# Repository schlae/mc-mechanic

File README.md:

# MC Mechanic - POST card for Micro Channel Computers
If you have an IBM PS/2 computer or one of the rare non-IBM Micro Channel computers, you know how hard it can be to debug boot issues. The IBM BIOS designs often do not use the PC speaker as extensively as other BIOSes, and a POST card is pretty much a requirement. However, not many were made back in the day and they are quite rare.

Fortunately, there is now a solution, the MC Mechanic. Not only can you get the standard PS/2 checkpoint codes at address 680h, but you can also spy on other addresses, which can be useful for troubleshooting. An additional bonus feature is the PS/2 info panel display. This lets you to see additional messages on PS/2 systems whose BIOS supports it but do not have the display itself. The PS/2 model 77 is one example, but there are probably others.

The components are reasonably available. The bill of materials lists Mouser part numbers, but the devices are all pretty common and can be purchased from a variety of overseas sources.

Here are the design files.

[Schematic](https://github.com/schlae/mc-mechanic/blob/main/mcapostcard.pdf)

[Bill of Materials](https://github.com/schlae/mc-mechanic/blob/main/mcapostcard.csv)

The 0.1" header pins are *not* listed on the schematic. They are standard breakaaway headers. You don't even have to install them since they are for advanced debugging with HP logic analyzer pods.

If you do not need the info panel display, then do not populate U10 and U8.

The design uses three GAL devices; two for driving the hex displays and one for decoding the address of the info panel (U8). The BOM specifies ATF16V8 devices because these are easy to get. The speed grade doesn't matter.

[Fab Files](https://github.com/schlae/mc-mechanic/blob/main/fab/mcapostcard-rev2.zip)

## Fabrication Notes
This is a 2-layer board sized for the lowest cost. The board dimensions are 3.925" x 3.475" (100mm x 88mm).

When ordering the board, you **must** specify a card edge bevel of 20 degrees (details of the bevel are included in the Dwgs.User layer). This is **not** optional! The contacts in the Micro Channel socket are easily bent if you attempt to insert a card with no bevel. [Don't believe me? See this page.](https://www.ardent-tool.com/RS6000/RS6000_9-K.html#ECA265)

Ideally you should use selective gold plating (hard gold) for the edge fingers, but this can get expensive for small orders. ENIG will work but the gold will rub off fairly quickly.

For the soldermask color, pick whatever you want!

## Assembly Notes

After you solder in the components, be sure to solder two jumper wires in the J4 position with the two wires aligned vertically (see the photo above). This configures the board for using the "normal" version of the hex rotary switches. If you decided to use the "complemented" version, then solder two jumper wires aligned horizontally.

You probably want to install the two (or three) GAL devices in sockets, just in case. The popular Minipro device programmer can be used to flash the ATF16V8 devices.

The command line for that (under Linux) looks like

`minipro -p "ATF16V8B" -w hexlatch.jed -P`

Here are the JEDEC files:

[hexlatch.jed](https://github.com/schlae/mc-mechanic/blob/main/pld/hexlatch.jed) - U6 and U7

[addrlatch.jed](https://github.com/schlae/mc-mechanic/blob/main/pld/addrlatch.jed) - U8

## Using the Card
Be sure to dial in an address using the four hex rotary switches. Unlike ISA bus machines, Micro Channel machines typically use address 0680h, so set SW4=0, SW3=6, SW2=8, and SW1=0. Plug the card in the computer, being careful to make sure it is pointed the right way around (there is an arrow underneath the two electrolytic capacitors pointing to the rear of the case of the computer.) Turn on the computer, and you should see three green LEDs (for the power rails) and a two-digit code that increments as the computer boots up.

For the meaning of the codes, see [this list of checkpoint codes](https://ardent-tool.com/trouble/cp_codes.html).

Messages also show up at the printer port address, 03BC. But feel free to explore and snoop any address you want using the hex rotary switches. As long as it is an IO port address that the computer *writes* to during standard IO transfers (not setup transfers), you will see data.

### Troubleshooting for Engineers
If you have an HP logic analyzer, like a 1670 or 16700 series, you can connect two cables to the card using standard HP 01650-63203 termination adapters. The pin assignments are as follows:

| HP | J2   |    J3   |
|----|------|---------|
| CLK | CMD# | ADL# |
| D0 | CHRESET | A0  |
| D1 | MIO  | A1  |
| D2 | S0# | A2 |
| D3 | CD\_SETUP# | A3 |
| D4 | LED\_SEL# | A4 |
| D5 | SEL1\_CMD# | A5 |
| D6 | n/c | A6 |
| D7 | A0 (latched) | A7 |
| D8 | D0 | A8 |
| D9 | D1 | A9 |
| D10 | D2 | A10 |
| D11 | D3 | A11 |
| D12 | D4 | A12 |
| D13 | D5 | A13 |
| D14 | D6 | A14 |
| D15 | D7 | A15 |

## License

This work is licensed under a Creative Commons Attribution-ShareAlike 4.0
International License. See [https://creativecommons.org/licenses/by-sa/4.0/](https://creativecommons.org/licenses/by-sa/4.0/).

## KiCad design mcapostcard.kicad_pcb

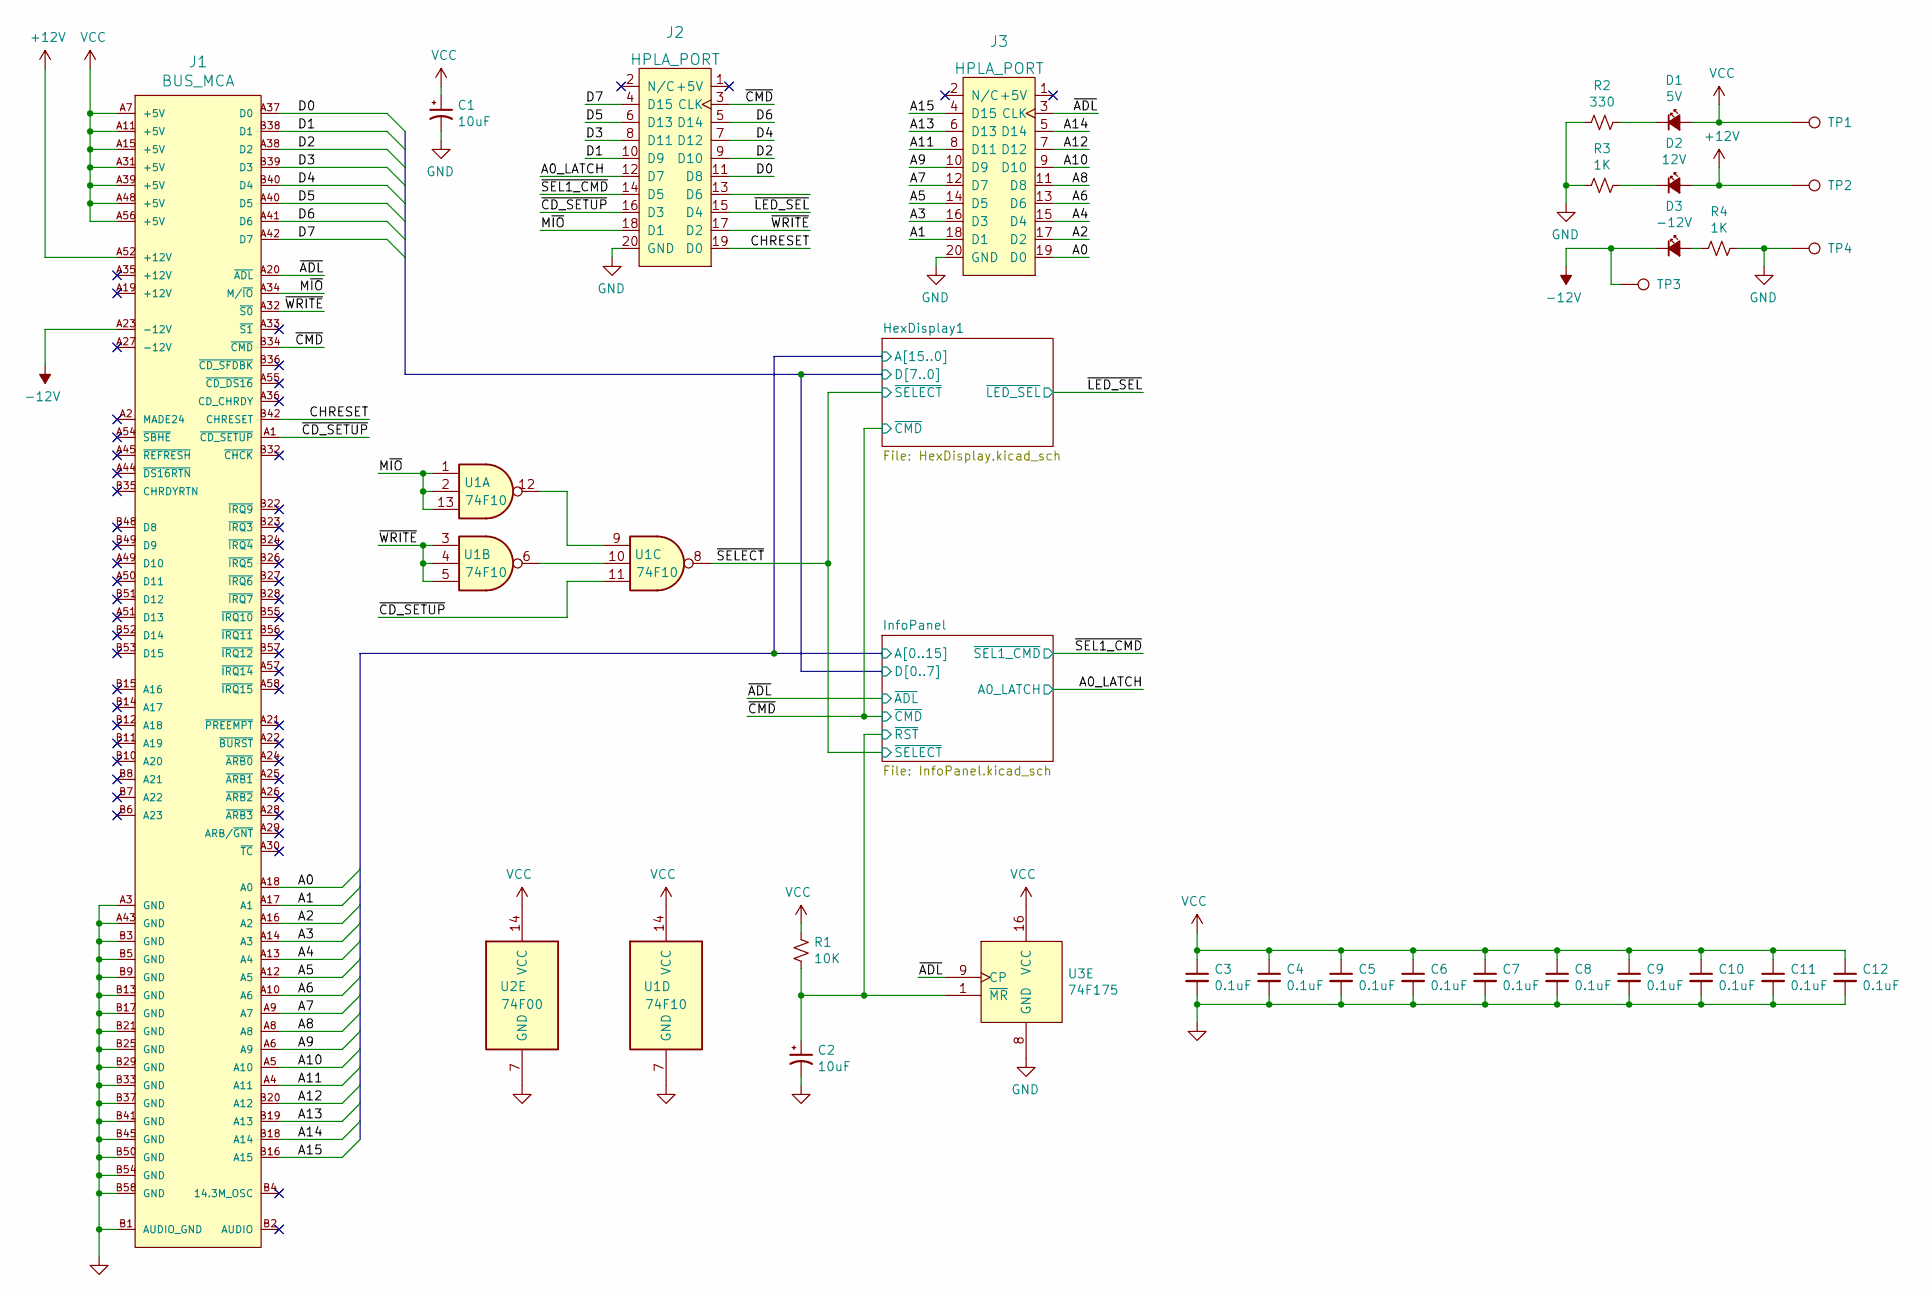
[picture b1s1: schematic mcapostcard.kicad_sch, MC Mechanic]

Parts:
C1, C2: 10uF; CAPAE200P500X1100; Mouser 667-ECA-1HM100I
C3, C4, C5, C6, C7, C8, C9, C10, C11, C12: 0.1uF; CAPAC200; Mouser 594-K104K15X7RF5TH5
D1: 5V; LED_D5.0mm; Mouser 604-WP7113SGD5V
D2: 12V; LED_D5.0mm; Mouser 604-WP7113SGD5V
D3: -12V; LED_D5.0mm; Mouser 604-WP7113SGD5V
J1: BUS_MCA
J2, J3: HPLA_PORT; PinHeader_2x10_P2.54mm_Vertical
R1: 10K; RESA500; Mouser 603-CFR-25JR-5210K
R2: 330; RESA500; Mouser 603-CFR-25JR-52330R
R3, R4: 1K; RESA500; Mouser 603-CFR-25JR-521K
TP1, TP2, TP3, TP4: TestPoint; TP_EDGE
U1: 74F10; DIP254P762X635-14; Mouser 595-SN74F10N
U2: 74F00; DIP254P762X635-14; Mouser 595-SN74F00NE4
U3: 74F175; DIP254P762X635-16; Mouser 595-SN74F175N

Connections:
+12V: D2.2 (A), J1.A52 (+12V), TP2.1
-12V: D3.1 (K), J1.A23 (-12V), TP3.1
/A0_LATCH: J2.12 (D7); also elsewhere on the board
/CHRESET: J1.B42 (CHRESET), J2.19 (D0)
/HexDisplay1/A0: J1.A18 (A0), J3.19 (D0); also elsewhere on the board
/HexDisplay1/A1: J1.A17 (A1), J3.18 (D1); also elsewhere on the board
/HexDisplay1/A2: J1.A16 (A2), J3.17 (D2); also elsewhere on the board
/HexDisplay1/A3: J1.A14 (A3), J3.16 (D3); also elsewhere on the board
/HexDisplay1/A4: J1.A13 (A4), J3.15 (D4); also elsewhere on the board
/HexDisplay1/A5: J1.A12 (A5), J3.14 (D5); also elsewhere on the board
/HexDisplay1/A6: J1.A10 (A6), J3.13 (D6); also elsewhere on the board
/HexDisplay1/A7: J1.A9 (A7), J3.12 (D7); also elsewhere on the board
/HexDisplay1/A8: J1.A8, J3.11 (D8); also elsewhere on the board
/HexDisplay1/A9: J1.A6 (A9), J3.10 (D9); also elsewhere on the board
/HexDisplay1/A10: J1.A5 (A10), J3.9 (D10); also elsewhere on the board
/HexDisplay1/A11: J1.A4 (A11), J3.8 (D11); also elsewhere on the board
/HexDisplay1/A12: J1.B20 (A12), J3.7 (D12); also elsewhere on the board
/HexDisplay1/A13: J1.B19 (A13), J3.6 (D13); also elsewhere on the board
/HexDisplay1/A14: J1.B18 (A14), J3.5 (D14); also elsewhere on the board
/HexDisplay1/A15: J1.B16 (A15), J3.4 (D15); also elsewhere on the board
/HexDisplay1/D0: J1.A37 (D0), J2.11 (D8); also elsewhere on the board
/HexDisplay1/D1: J1.B38 (D1), J2.10 (D9); also elsewhere on the board
/HexDisplay1/D2: J1.A38 (D2), J2.9 (D10); also elsewhere on the board
/HexDisplay1/D3: J1.B39 (D3), J2.8 (D11); also elsewhere on the board
/HexDisplay1/D4: J1.B40 (D4), J2.7 (D12); also elsewhere on the board
/HexDisplay1/D5: J1.A40 (D5), J2.6 (D13); also elsewhere on the board
/HexDisplay1/D6: J1.A41 (D6), J2.5 (D14); also elsewhere on the board
/HexDisplay1/D7: J1.A42 (D7), J2.4 (D15); also elsewhere on the board
/InfoPanel/~RST: C2.1, R1.2, U3.1 (~MR); also elsewhere on the board
/M~IO: J1.A34 (M/~IO), J2.18 (D1), U1.1, U1.2, U1.13
/~ADL: J1.A20 (~ADL), J3.3 (CLK), U3.9 (CP); also elsewhere on the board
/~CD_SETUP: J1.A1 (~CD_SETUP), J2.16 (D3), U1.11
/~CMD: J1.B34 (~CMD), J2.3 (CLK); also elsewhere on the board
/~LED_SEL: J2.15 (D4); also elsewhere on the board
/~SEL1_CMD: J2.14 (D5); also elsewhere on the board
/~SELECT: U1.8; also elsewhere on the board
/~WRITE: J1.A32 (~S0), J2.17 (D2), U1.3, U1.4, U1.5
GND: C1.2, C2.2, C3.2, C4.2, C5.2, C6.2, C7.2, C8.2, C9.2, C10.2, C11.2, C12.2, J1.A3 (GND), J1.A43 (GND), J1.B1 (AUDIO_GND), J1.B3 (GND), J1.B5 (GND), J1.B9 (GND), J1.B13 (GND), J1.B17 (GND), J1.B21 (GND), J1.B25 (GND), J1.B29 (GND), J1.B33 (GND), J1.B37 (GND), J1.B41 (GND), J1.B45 (GND), J1.B50 (GND), J1.B54 (GND), J1.B58 (GND), J2.20 (GND), J3.20 (GND), R2.2, R3.2, R4.1, TP4.1, U1.7 (GND), U2.7 (GND), U3.8 (GND); also elsewhere on the board
unnamed: D1.1 (K), R2.1
unnamed: D2.1 (K), R3.1
unnamed: D3.2 (A), R4.2
unnamed: U1.6, U1.10
unnamed: U1.9, U1.12
VCC: C1.1, C3.1, C4.1, C5.1, C6.1, C7.1, C8.1, C9.1, C10.1, C11.1, C12.1, D1.2 (A), J1.A7 (+5V), J1.A11 (+5V), J1.A15 (+5V), J1.A31 (+5V), J1.A39 (+5V), J1.A48 (+5V), J1.A56 (+5V), R1.1, TP1.1, U1.14 (VCC), U2.14 (VCC), U3.16 (VCC); also elsewhere on the board

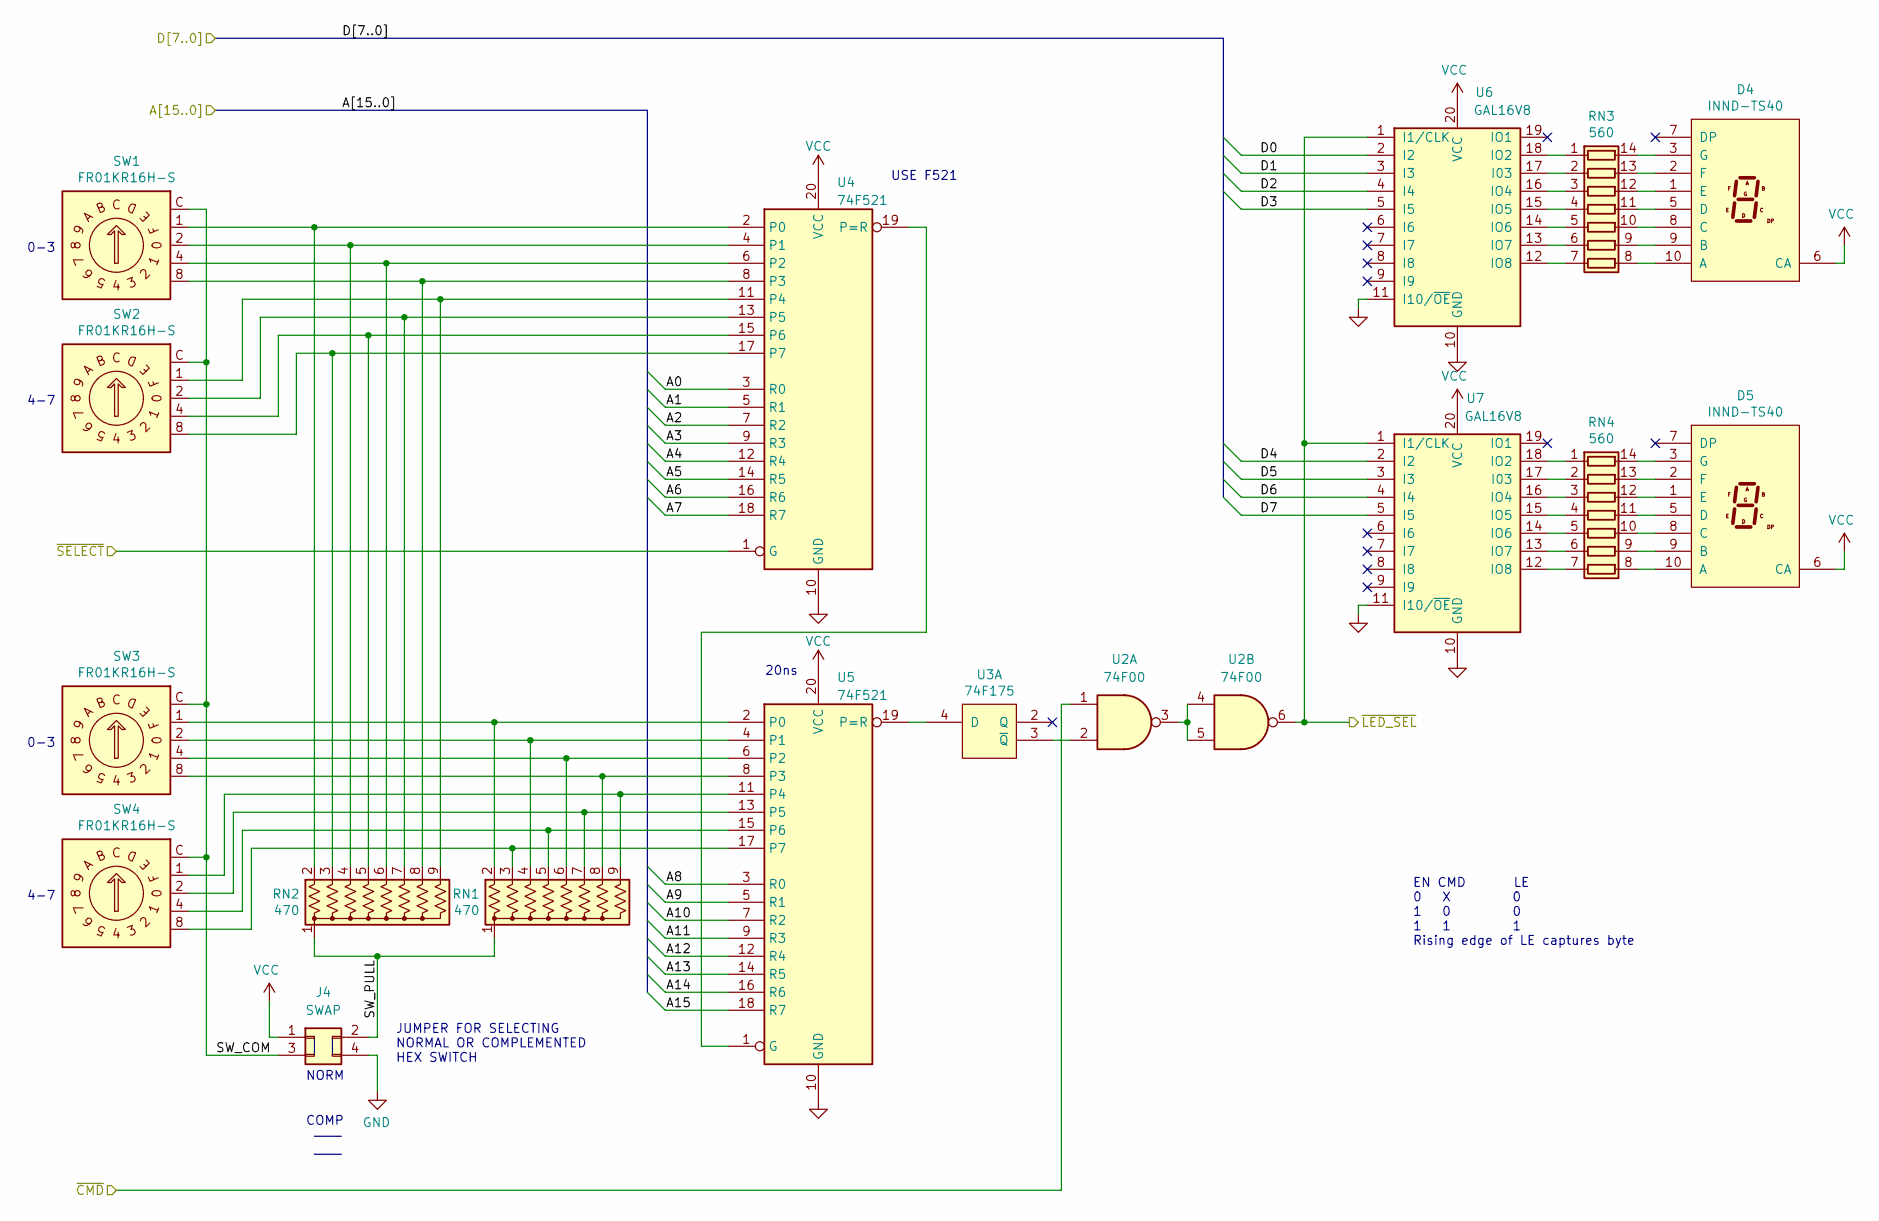
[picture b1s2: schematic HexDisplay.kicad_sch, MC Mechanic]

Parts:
D4, D5: INND-TS40; MPN INND-TS40RAB; Mouser 743-INND-TS40RAB
J4: SWAP; PinHeader_2x02_P2.54mm_Vertical
RN1, RN2: 470; R_Array_SIP9; Mouser 652-4609X-AP1-471LF
RN3, RN4: 560; DIP254P762X635-14; Mouser 652-4114R-1LF-560
SW1, SW2, SW3, SW4: FR01KR16H-S; NKK_FR01KR16H; MPN FR01KR16H-S; Mouser 633-FR01KR16H-S
U2: 74F00; DIP254P762X635-14; Mouser 595-SN74F00NE4
U3: 74F175; DIP254P762X635-16; Mouser 595-SN74F175N
U4, U5: 74F521; DIP254P762X635-20; Mouser 595-SN74F521N
U6, U7: GAL16V8; DIP254P762X635-20; Mouser 556-AF16V8CZ15PU

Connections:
/HexDisplay1/A0: U4.3 (R0); also elsewhere on the board
/HexDisplay1/A1: U4.5 (R1); also elsewhere on the board
/HexDisplay1/A2: U4.7 (R2); also elsewhere on the board
/HexDisplay1/A3: U4.9 (R3); also elsewhere on the board
/HexDisplay1/A4: U4.12 (R4); also elsewhere on the board
/HexDisplay1/A5: U4.14 (R5); also elsewhere on the board
/HexDisplay1/A6: U4.16 (R6); also elsewhere on the board
/HexDisplay1/A7: U4.18 (R7); also elsewhere on the board
/HexDisplay1/A8: U5.3 (R0); also elsewhere on the board
/HexDisplay1/A9: U5.5 (R1); also elsewhere on the board
/HexDisplay1/A10: U5.7 (R2); also elsewhere on the board
/HexDisplay1/A11: U5.9 (R3); also elsewhere on the board
/HexDisplay1/A12: U5.12 (R4); also elsewhere on the board
/HexDisplay1/A13: U5.14 (R5); also elsewhere on the board
/HexDisplay1/A14: U5.16 (R6); also elsewhere on the board
/HexDisplay1/A15: U5.18 (R7); also elsewhere on the board
/HexDisplay1/D0: U6.2 (I2); also elsewhere on the board
/HexDisplay1/D1: U6.3 (I3); also elsewhere on the board
/HexDisplay1/D2: U6.4 (I4); also elsewhere on the board
/HexDisplay1/D3: U6.5 (I5); also elsewhere on the board
/HexDisplay1/D4: U7.2 (I2); also elsewhere on the board
/HexDisplay1/D5: U7.3 (I3); also elsewhere on the board
/HexDisplay1/D6: U7.4 (I4); also elsewhere on the board
/HexDisplay1/D7: U7.5 (I5); also elsewhere on the board
/HexDisplay1/SW_COM: J4.3, SW1.C, SW2.C, SW3.C, SW4.C
/HexDisplay1/SW_PULL: J4.2, RN1.1 (common), RN2.1 (common)
/~CMD: U2.1; also elsewhere on the board
/~LED_SEL: U2.6, U6.1 (I1/CLK), U7.1 (I1/CLK); also elsewhere on the board
/~SELECT: U4.1 (G); also elsewhere on the board
GND: J4.4, U4.10 (GND), U5.10 (GND), U6.10 (GND), U6.11 (I10/~OE), U7.10 (GND), U7.11 (I10/~OE); also elsewhere on the board
unnamed: D4.1 (E), RN3.12 (R3.2)
unnamed: D4.2 (F), RN3.13 (R2.2)
unnamed: D4.3 (G), RN3.14 (R1.2)
unnamed: D4.5 (D), RN3.11 (R4.2)
unnamed: D4.8 (C), RN3.10 (R5.2)
unnamed: D4.9 (B), RN3.9 (R6.2)
unnamed: D4.10 (A), RN3.8 (R7.2)
unnamed: D5.1 (E), RN4.12 (R3.2)
unnamed: D5.2 (F), RN4.13 (R2.2)
unnamed: D5.3 (G), RN4.14 (R1.2)
unnamed: D5.5 (D), RN4.11 (R4.2)
unnamed: D5.8 (C), RN4.10 (R5.2)
unnamed: D5.9 (B), RN4.9 (R6.2)
unnamed: D5.10 (A), RN4.8 (R7.2)
unnamed: RN1.2 (R1), SW3.1, U5.2 (P0)
unnamed: RN1.3 (R2), SW4.8, U5.17 (P7)
unnamed: RN1.4 (R3), SW3.2, U5.4 (P1)
unnamed: RN1.5 (R4), SW4.4, U5.15 (P6)
unnamed: RN1.6 (R5), SW3.4, U5.6 (P2)
unnamed: RN1.7 (R6), SW4.2, U5.13 (P5)
unnamed: RN1.8 (R7), SW3.8, U5.8 (P3)
unnamed: RN1.9 (R8), SW4.1, U5.11 (P4)
unnamed: RN2.2 (R1), SW1.1, U4.2 (P0)
unnamed: RN2.3 (R2), SW2.8, U4.17 (P7)
unnamed: RN2.4 (R3), SW1.2, U4.4 (P1)
unnamed: RN2.5 (R4), SW2.4, U4.15 (P6)
unnamed: RN2.6 (R5), SW1.4, U4.6 (P2)
unnamed: RN2.7 (R6), SW2.2, U4.13 (P5)
unnamed: RN2.8 (R7), SW1.8, U4.8 (P3)
unnamed: RN2.9 (R8), SW2.1, U4.11 (P4)
unnamed: RN3.1 (R1.1), U6.18 (IO2)
unnamed: RN3.2 (R2.1), U6.17 (I03)
unnamed: RN3.3 (R3.1), U6.16 (IO4)
unnamed: RN3.4 (R4.1), U6.15 (IO5)
unnamed: RN3.5 (R5.1), U6.14 (IO6)
unnamed: RN3.6 (R6.1), U6.13 (IO7)
unnamed: RN3.7 (R7.1), U6.12 (IO8)
unnamed: RN4.1 (R1.1), U7.18 (IO2)
unnamed: RN4.2 (R2.1), U7.17 (I03)
unnamed: RN4.3 (R3.1), U7.16 (IO4)
unnamed: RN4.4 (R4.1), U7.15 (IO5)
unnamed: RN4.5 (R5.1), U7.14 (IO6)
unnamed: RN4.6 (R6.1), U7.13 (IO7)
unnamed: RN4.7 (R7.1), U7.12 (IO8)
unnamed: U2.2, U3.3 (~Q)
unnamed: U2.3, U2.4, U2.5
unnamed: U3.4 (D), U5.19 (P=R)
unnamed: U4.19 (P=R), U5.1 (G)
VCC: D4.6 (CA), D5.6 (CA), J4.1, U4.20 (VCC), U5.20 (VCC), U6.20 (VCC), U7.20 (VCC); also elsewhere on the board

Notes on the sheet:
NORM
USE F521
4-7
EN CMD LE 0 X 0 1 0 0 1 1 1 Rising edge of LE captures byte
0-3
JUMPER FOR SELECTING NORMAL OR COMPLEMENTED HEX SWITCH
20ns
COMP

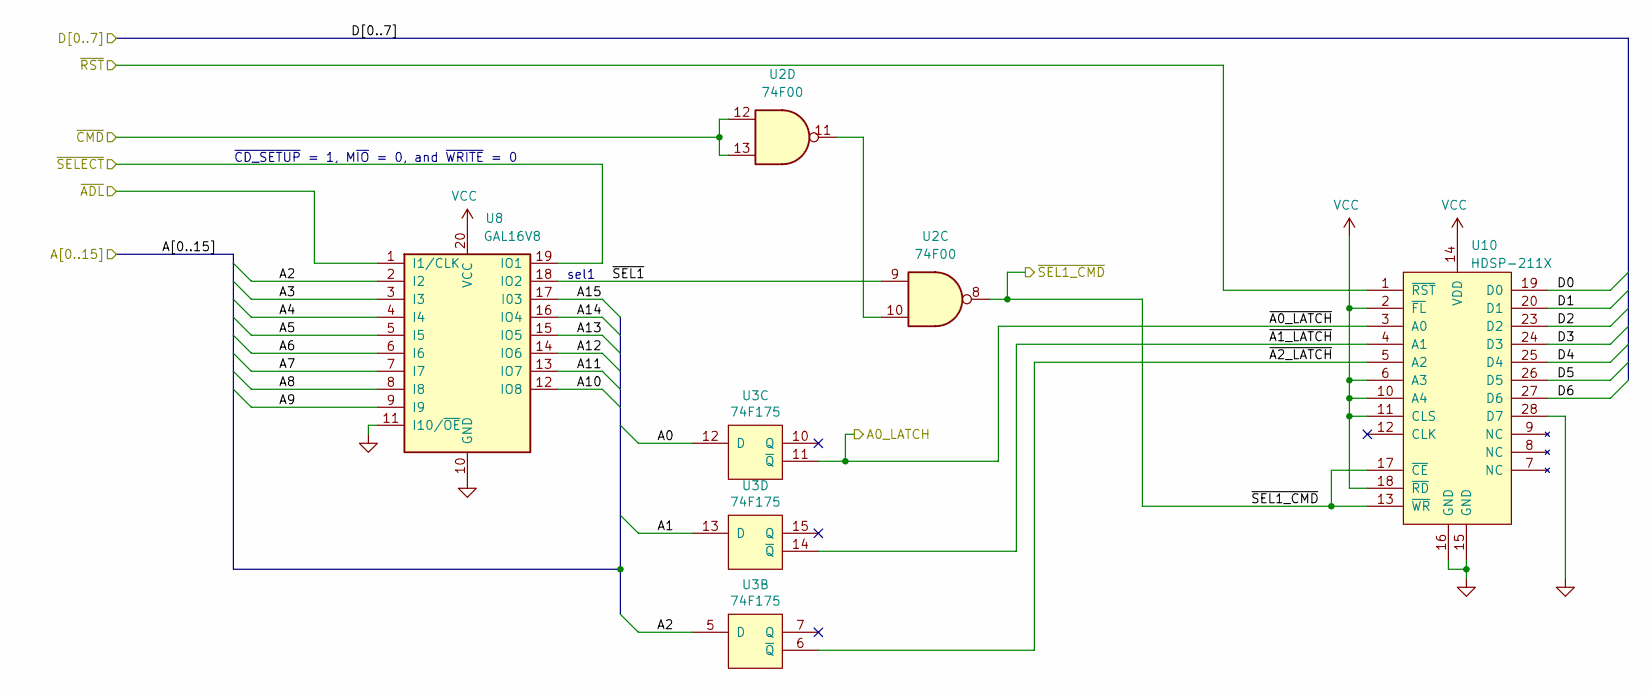
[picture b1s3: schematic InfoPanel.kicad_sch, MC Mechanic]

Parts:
U2: 74F00; DIP254P762X635-14; Mouser 595-SN74F00NE4
U3: 74F175; DIP254P762X635-16; Mouser 595-SN74F175N
U8: GAL16V8; DIP254P762X635-20; Mouser 556-AF16V8CZ15PU
U10: HDSP-211X; Mouser 630-HDSP-2113

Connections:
/A0_LATCH: U3.11 (~Q), U10.3 (A0); also elsewhere on the board
/HexDisplay1/A0: U3.12 (D); also elsewhere on the board
/HexDisplay1/A1: U3.13 (D); also elsewhere on the board
/HexDisplay1/A2: U3.5 (D), U8.2 (I2); also elsewhere on the board
/HexDisplay1/A3: U8.3 (I3); also elsewhere on the board
/HexDisplay1/A4: U8.4 (I4); also elsewhere on the board
/HexDisplay1/A5: U8.5 (I5); also elsewhere on the board
/HexDisplay1/A6: U8.6 (I6); also elsewhere on the board
/HexDisplay1/A7: U8.7 (I7); also elsewhere on the board
/HexDisplay1/A8: U8.8 (I8); also elsewhere on the board
/HexDisplay1/A9: U8.9 (I9); also elsewhere on the board
/HexDisplay1/A10: U8.12 (IO8); also elsewhere on the board
/HexDisplay1/A11: U8.13 (IO7); also elsewhere on the board
/HexDisplay1/A12: U8.14 (IO6); also elsewhere on the board
/HexDisplay1/A13: U8.15 (IO5); also elsewhere on the board
/HexDisplay1/A14: U8.16 (IO4); also elsewhere on the board
/HexDisplay1/A15: U8.17 (I03); also elsewhere on the board
/HexDisplay1/D0: U10.19 (D0); also elsewhere on the board
/HexDisplay1/D1: U10.20 (D1); also elsewhere on the board
/HexDisplay1/D2: U10.23 (D2); also elsewhere on the board
/HexDisplay1/D3: U10.24 (D3); also elsewhere on the board
/HexDisplay1/D4: U10.25 (D4); also elsewhere on the board
/HexDisplay1/D5: U10.26 (D5); also elsewhere on the board
/HexDisplay1/D6: U10.27 (D6); also elsewhere on the board
/InfoPanel/~A1_LATCH: U3.14 (~Q), U10.4 (A1)
/InfoPanel/~A2_LATCH: U3.6 (~Q), U10.5 (A2)
/InfoPanel/~RST: U10.1 (~RST); also elsewhere on the board
/InfoPanel/~SEL1: U2.9, U8.18 (IO2)
/~ADL: U8.1 (I1/CLK); also elsewhere on the board
/~CMD: U2.12, U2.13; also elsewhere on the board
/~SEL1_CMD: U2.8, U10.13 (~WR), U10.17 (~CE); also elsewhere on the board
/~SELECT: U8.19 (IO1); also elsewhere on the board
GND: U8.10 (GND), U8.11 (I10/~OE), U10.15 (GND), U10.16 (GND), U10.28 (D7); also elsewhere on the board
unnamed: U2.10, U2.11
VCC: U8.20 (VCC), U10.2 (~FL), U10.6 (A3), U10.10 (A4), U10.11 (CLS), U10.14 (VDD), U10.18 (~RD); also elsewhere on the board

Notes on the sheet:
~{CD_SETUP} = 1, M~{IO} = 0, and ~{WRITE} = 0
sel1

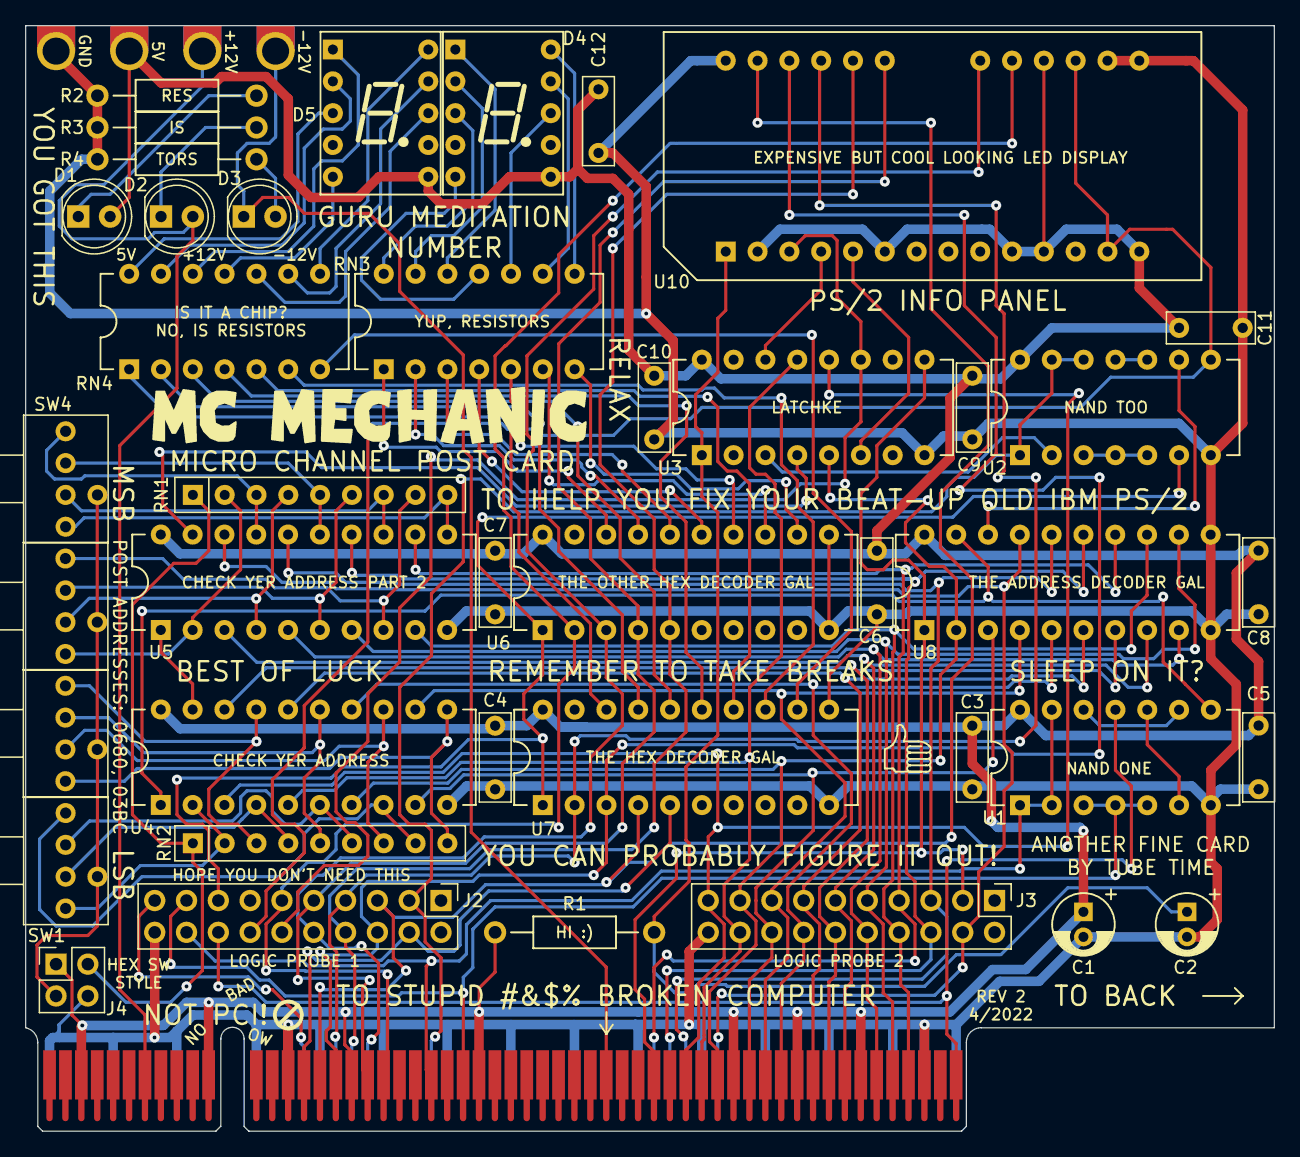
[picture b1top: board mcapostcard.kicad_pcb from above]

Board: 2 copper layers, 99.7 x 88.3 mm, 46 parts (0 on the bottom side), 98 nets.

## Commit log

2022-05-11 add project files

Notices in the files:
HexDisplay.kicad_sch:
(C) 2022 Tube Time
http://creativecommons.org/licenses/by-sa/4.0
This work is licensed under the Creative Commons
